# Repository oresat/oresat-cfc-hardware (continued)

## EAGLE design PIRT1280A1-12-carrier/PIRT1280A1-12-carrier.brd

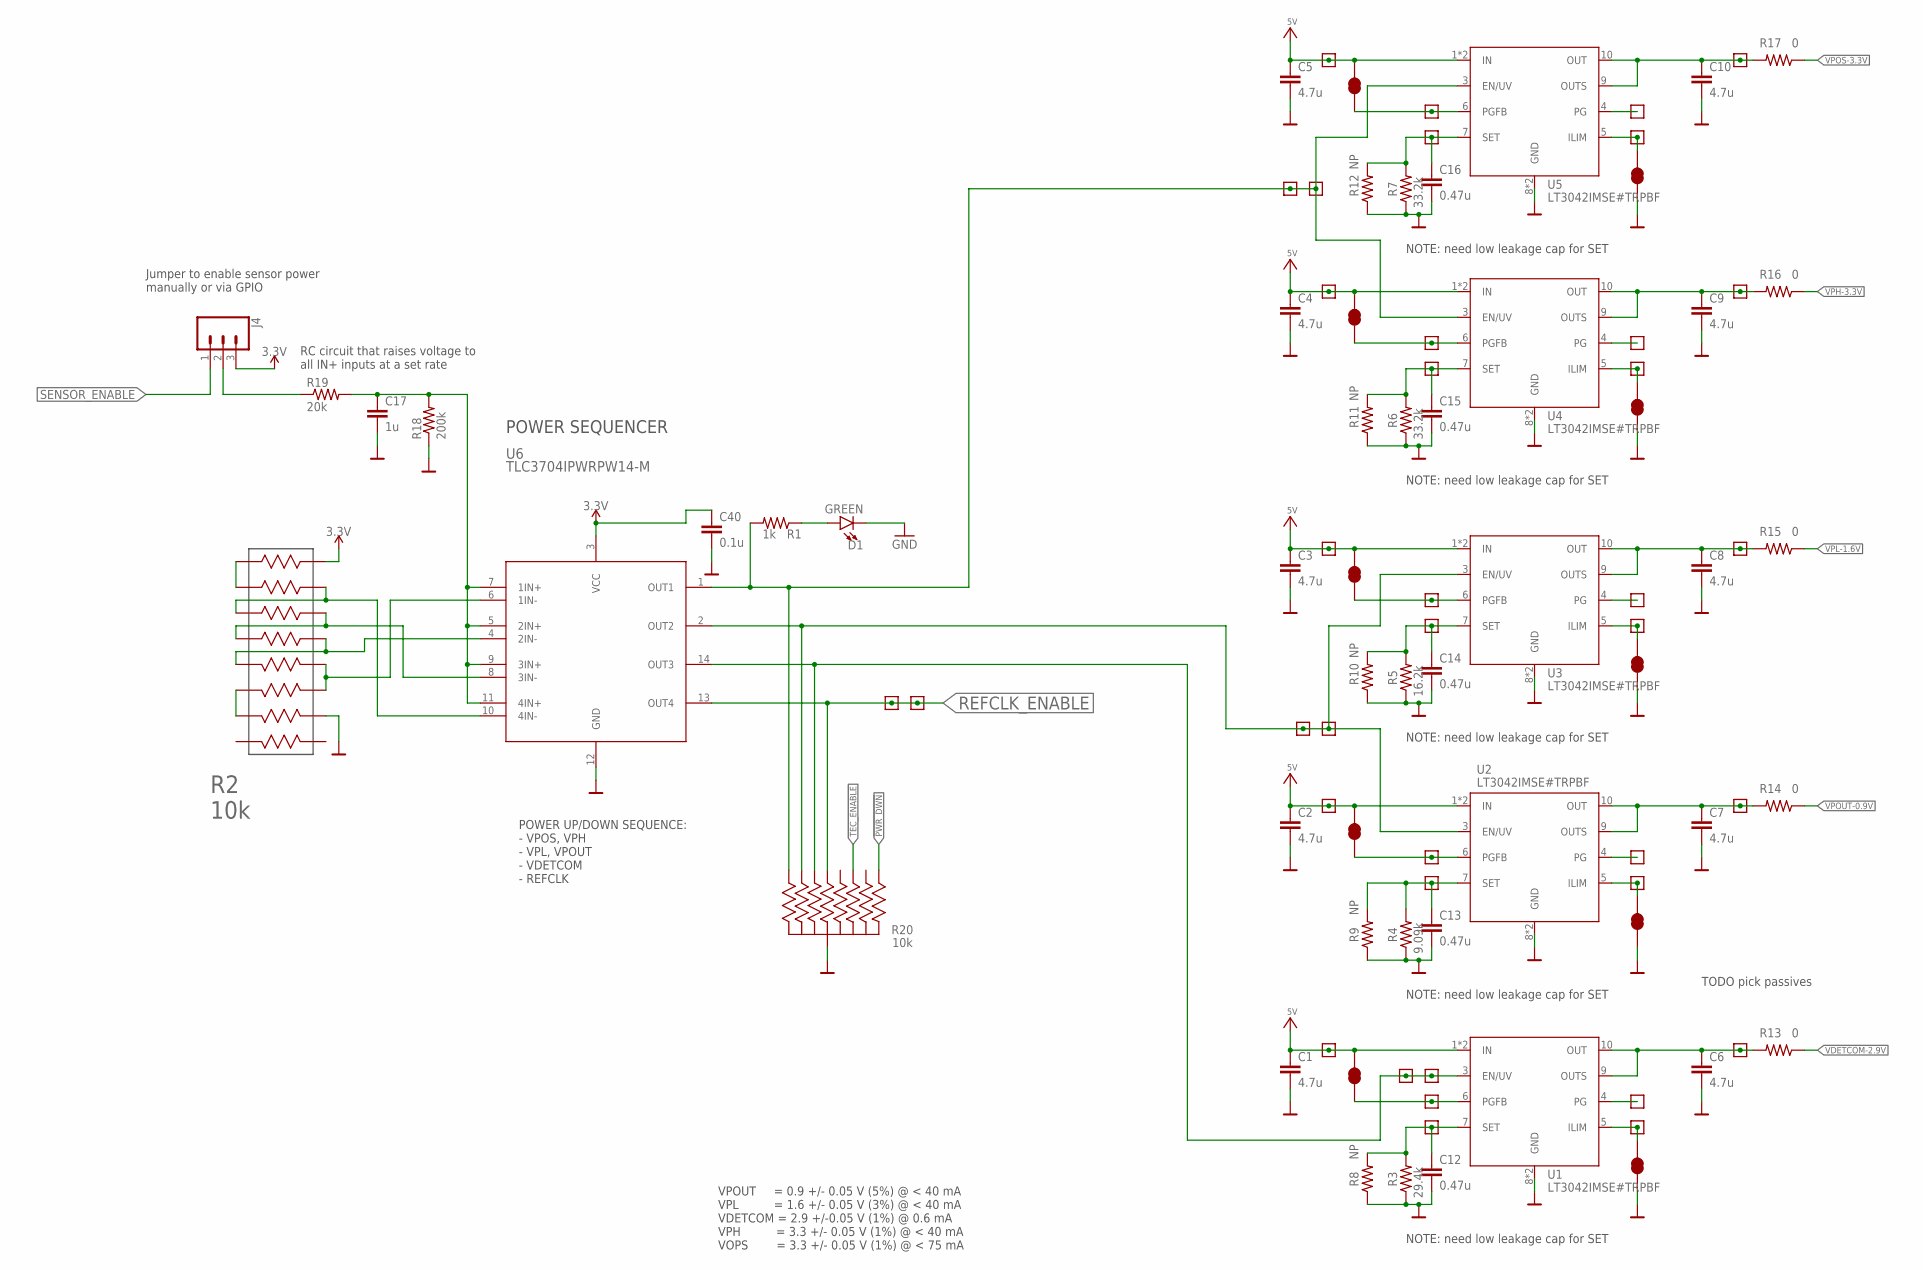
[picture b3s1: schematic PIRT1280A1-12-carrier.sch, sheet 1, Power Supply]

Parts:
C1, C2, C3, C4, C5, C6, C7, C8, C9, C10: 4.7u; .0603-A
C12, C13, C14, C15, C16: 0.47u; .0603-A
C17: 1u; .0603-A
C40: 0.1u; .0603-A
D1: GREEN; LED-0603; MANUFACTURER_PART_NUMBER 150060VS55040; DIGI-KEY_PART_NUMBER 732-12017-1-ND
J4: 455-1750-1-ND; 1X03
R1: 1k; .0603-A
R2: 10k; RES_EXB2HV
R3: 29.4k; .0603-A
R4: 9.09k; .0603-A
R5: 16.2k; .0603-A
R6, R7: 33.2k; .0603-A
R8, R9, R10, R11, R12: NP; .0603-A
R13, R14, R15, R16, R17: 0; .0603-A
R18: 200k; .0805-A
R19: 20k; .0805-A
R20: 10k; ARRAY_EXBA-M; MPN EXB-A10P103J
SJ1, SJ2, SJ3, SJ4, SJ5, SJ6, SJ7, SJ8, SJ9, SJ10: JUMPER-SMT_2_NC_TRACE_NO-SILK; SMT-JUMPER_2_NC_TRACE_NO-SILK
TP1, TP2, TP3, TP4, TP5, TP6, TP7, TP8, TP9, TP10, TP11, TP12, TP13, TP14, TP15, TP16, TP17, TP18, TP19, TP20, TP21, TP22, TP23, TP24, TP25, TP26, TP27, TP28, TP29, TP30, TP31, TP32, TP33, TP34, TP35, TP36, TP37, TP38: TEST-POINT-LARGE-SQUARE; 1X01
U1, U2, U3, U4, U5: LT3042IMSE#TRPBF; SOP50P490X110-11N
U6: TLC3704IPWRPW14-M; 14-TSSOP

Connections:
3.3V: C40.1, J4.3, R2.16, U6.3 (VCC); also elsewhere on the board
5V: C1.1, C2.1, C3.1, C4.1, C5.1, SJ6.2, SJ7.2, SJ8.2, SJ9.2, SJ10.2, TP3.1, TP6.1, TP9.1, TP12.1, TP15.1, U1.1 (IN), U1.2 (IN), U2.1 (IN), U2.2 (IN), U3.1 (IN), U3.2 (IN), U4.1 (IN), U4.2 (IN), U5.1 (IN), U5.2 (IN); also elsewhere on the board
!PWR_DWN: R20.1 (11); also elsewhere on the board
GND: C1.2, C2.2, C3.2, C4.2, C5.2, C6.2, C7.2, C8.2, C9.2, C10.2, C12.2, C13.2, C14.2, C15.2, C16.2, C17.2, C40.2, D1.C, R2.10, R3.1, R4.1, R5.1, R6.1, R7.1, R8.1, R9.1, R10.1, R11.1, R12.1, R18.1, R20.5 (55), R20.10 (55), SJ1.1, SJ2.1, SJ3.1, SJ4.1, SJ5.1, U1.8 (GND), U1.11 (GND), U2.8 (GND), U2.11 (GND), U3.8 (GND), U3.11 (GND), U4.8 (GND), U4.11 (GND), U5.8 (GND), U5.11 (GND), U6.12 (GND); also elsewhere on the board
unnamed: R2.1, R2.2
unnamed: R2.3, R2.15, U6.10 (4IN-)
unnamed: R2.4, R2.14, U6.8 (3IN-)
unnamed: R2.5, R2.13, U6.4 (2IN-)
unnamed: C17.1, R18.2, R19.2, U6.5 (2IN+), U6.7 (1IN+), U6.9 (3IN+), U6.11 (4IN+)
unnamed: R2.6, R2.7
unnamed: R20.7 (77), TP20.1, TP21.1, U1.3 (EN/UV), U6.14 (OUT3)
unnamed: SJ7.1, TP31.1, U2.6 (PGFB)
unnamed: SJ2.2, TP4.1, U2.5 (ILIM)
unnamed: TP5.1, U2.4 (PG)
unnamed: J4.2, R19.1
unnamed: C13.1, R4.2, R9.2, TP32.1, U2.7 (SET)
unnamed: SJ1.2, TP1.1, U1.5 (ILIM)
unnamed: SJ6.1, TP29.1, U1.6 (PGFB)
unnamed: TP2.1, U1.4 (PG)
unnamed: C12.1, R3.2, R8.2, TP30.1, U1.7 (SET)
unnamed: R1.2, R20.6 (66), TP16.1, TP17.1, U4.3 (EN/UV), U5.3 (EN/UV), U6.1 (OUT1)
unnamed: SJ5.2, TP13.1, U5.5 (ILIM)
unnamed: SJ10.1, TP37.1, U5.6 (PGFB)
unnamed: TP14.1, U5.4 (PG)
unnamed: C16.1, R7.2, R12.2, TP38.1, U5.7 (SET)
unnamed: SJ4.2, TP10.1, U4.5 (ILIM)
unnamed: SJ9.1, TP35.1, U4.6 (PGFB)
unnamed: TP11.1, U4.4 (PG)
unnamed: C15.1, R6.2, R11.2, TP36.1, U4.7 (SET)
unnamed: R20.4 (44), TP18.1, TP19.1, U2.3 (EN/UV), U3.3 (EN/UV), U6.2 (OUT2)
unnamed: SJ3.2, TP7.1, U3.5 (ILIM)
unnamed: SJ8.1, TP33.1, U3.6 (PGFB)
unnamed: TP8.1, U3.4 (PG)
unnamed: C14.1, R5.2, R10.2, TP34.1, U3.7 (SET)
unnamed: R2.11, R2.12, U6.6 (1IN-)
unnamed: D1.A, R1.1
REFCLK_ENABLE: R20.3 (33), TP27.1, TP28.1, U6.13 (OUT4); also elsewhere on the board
SENSOR_ENABLE: J4.1; also elsewhere on the board
TEC_ENABLE: R20.2 (22); also elsewhere on the board
VDETCOM: C6.1, R13.2, TP22.1, U1.9 (OUTS), U1.10 (OUT)
VDETCOM-2.9V: R13.1; also elsewhere on the board
VPH: C9.1, R16.2, TP25.1, U4.9 (OUTS), U4.10 (OUT)
VPH-3.3V: R16.1; also elsewhere on the board
VPL: C8.1, R15.2, TP24.1, U3.9 (OUTS), U3.10 (OUT)
VPL-1.6V: R15.1; also elsewhere on the board
VPOS: C10.1, R17.2, TP26.1, U5.9 (OUTS), U5.10 (OUT)
VPOS-3.3V: R17.1; also elsewhere on the board
VPOUT: C7.1, R14.2, TP23.1, U2.9 (OUTS), U2.10 (OUT)
VPOUT-0.9V: R14.1; also elsewhere on the board

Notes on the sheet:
VPOUT = 0.9 +/- 0.05 V (5%) @ < 40 mA VPL = 1.6 +/- 0.05 V (3%) @ < 40 mA VDETCOM = 2.9 +/-0.05 V (1%) @ 0.6 mA VPH = 3.3 +/- 0.05 V (1%) @ < 40 mA VOPS = 3.3 +/- 0.05 V (1%) @ < 75 mA
NOTE: need low leakage cap for SET
TODO pick passives
POWER UP/DOWN SEQUENCE: - VPOS, VPH - VPL, VPOUT - VDETCOM - REFCLK
RC circuit that raises voltage to all IN+ inputs at a set rate
Jumper to enable sensor power manually or via GPIO
POWER SEQUENCER

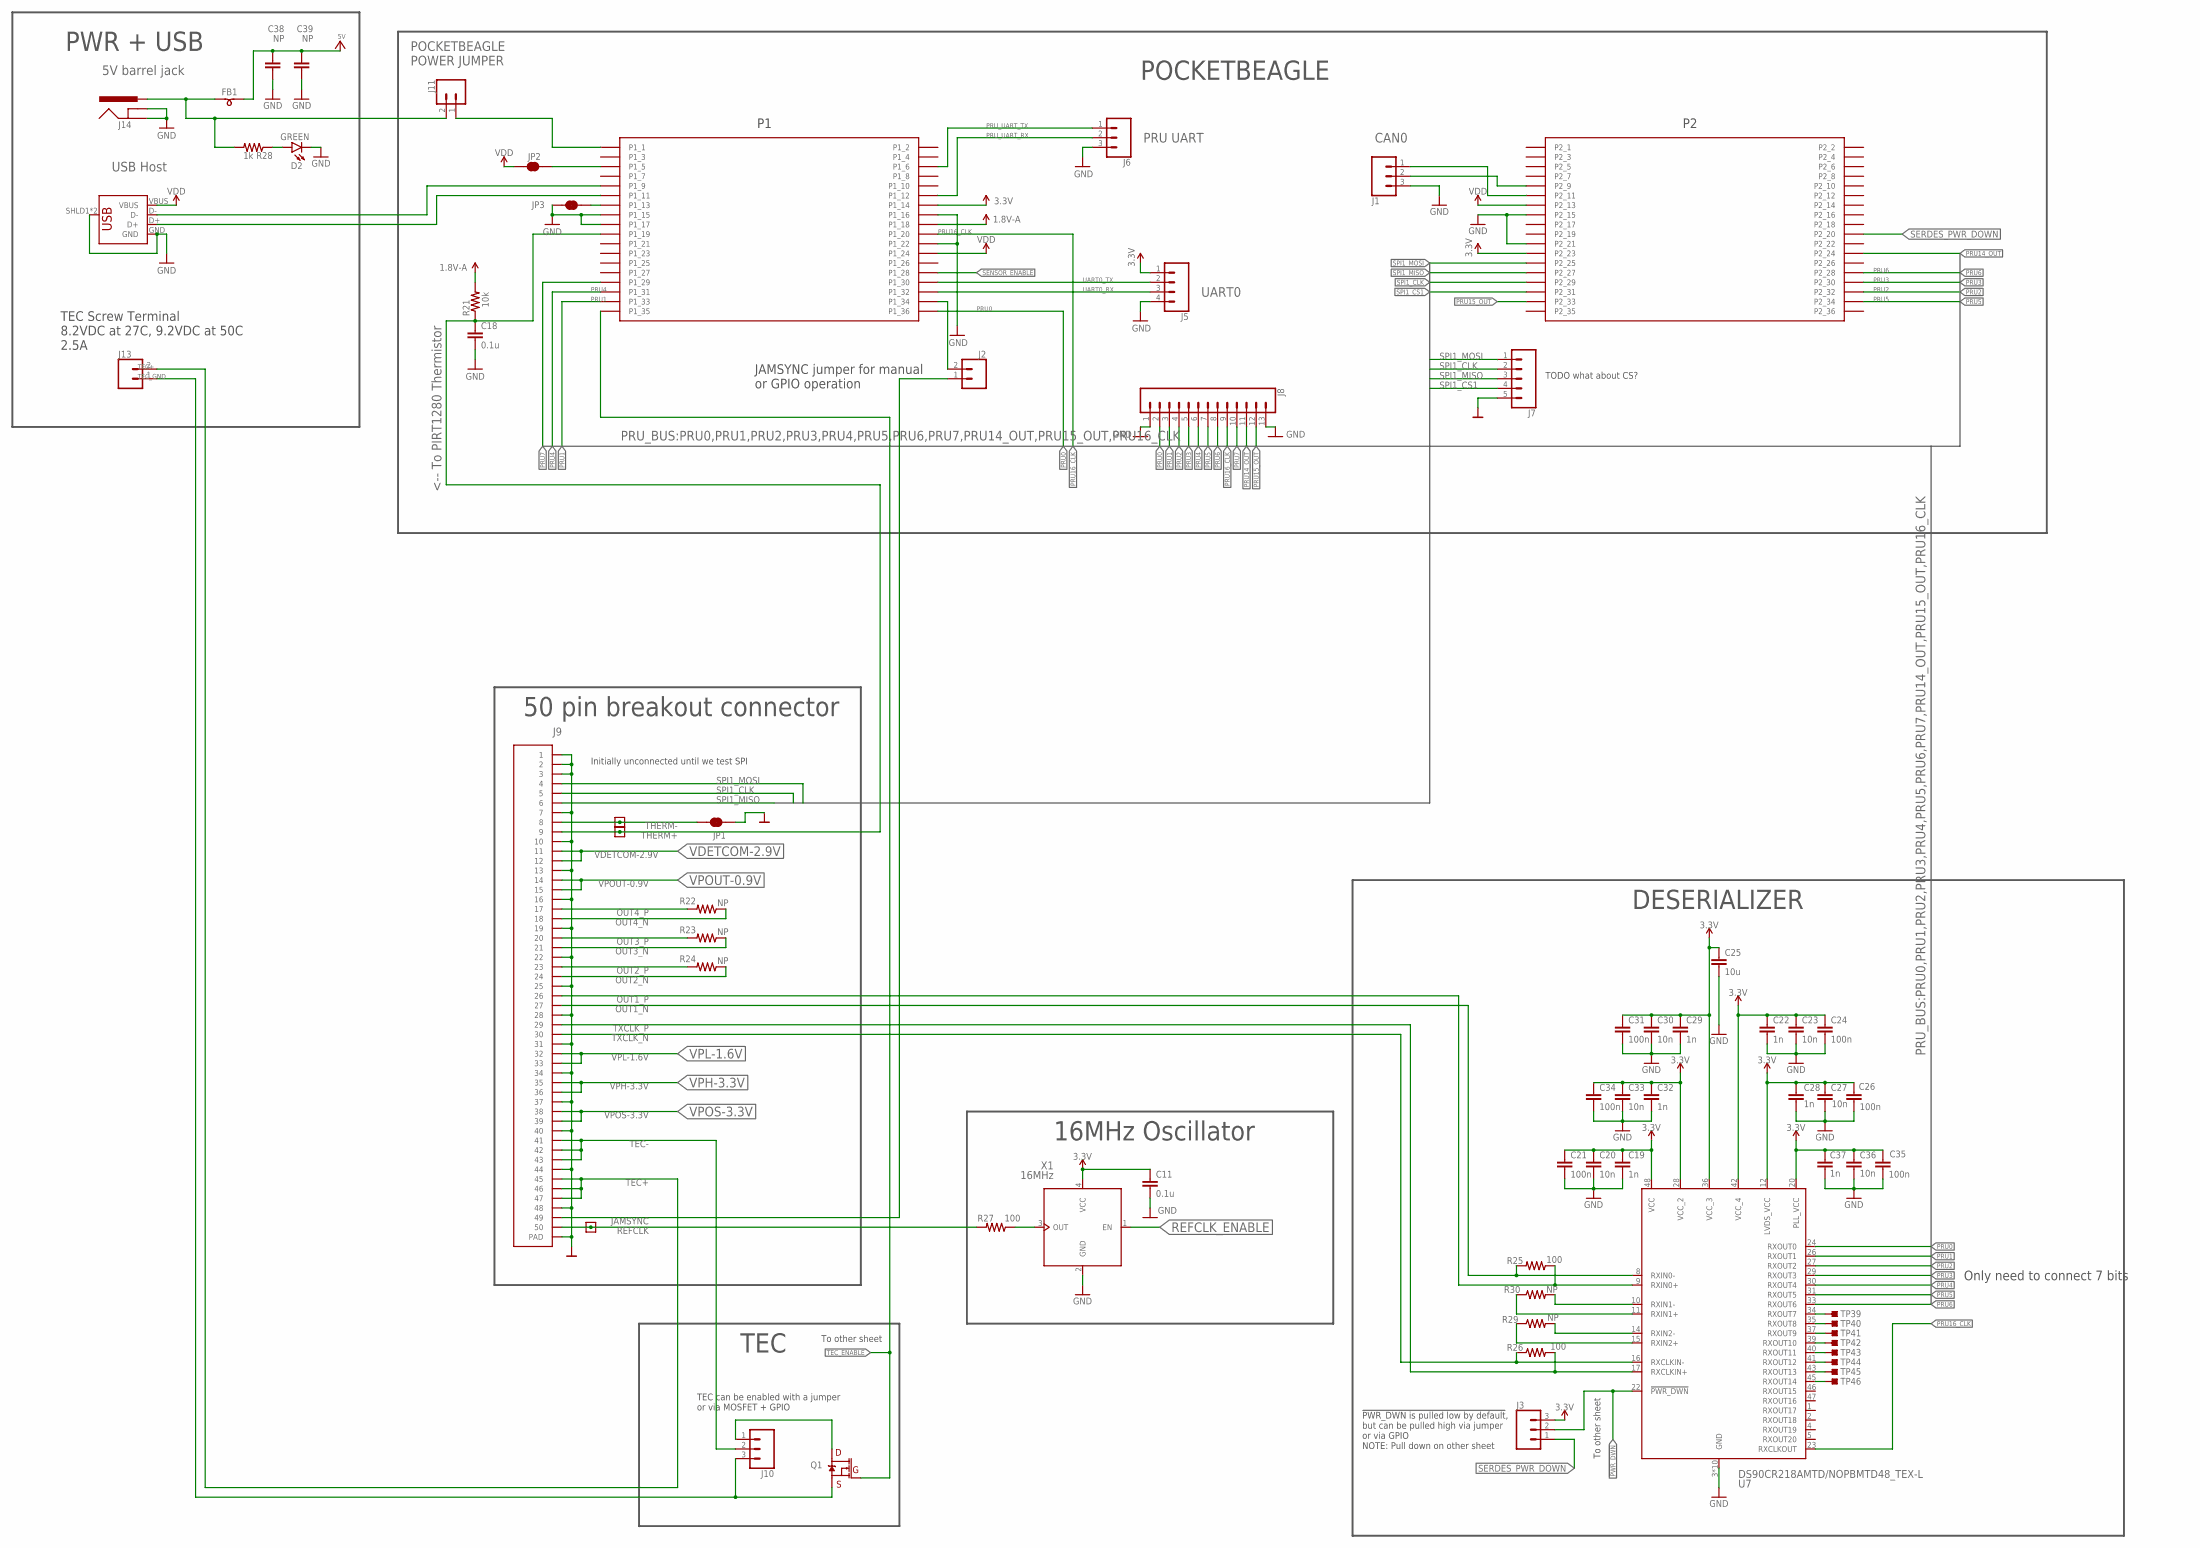
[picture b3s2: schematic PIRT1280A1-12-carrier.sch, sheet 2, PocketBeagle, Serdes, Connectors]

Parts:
C11, C18: 0.1u; .0603-A
C19, C22, C28, C29, C32, C37: 1n; .0402-C-NOSILK; MPN GRM155R71H102KA01J
C20, C23, C27, C30, C33, C36: 10n; .0402-C-NOSILK; MPN C0603C103M5RACTU
C21, C24, C26, C31, C34, C35: 100n; .0402-C-NOSILK; MPN C0805C104Z5VACTU
C25: 10u; .0603-C-NOSILK; MPN GRM188R61A106KE69J
C38, C39: NP; C1210
D2: GREEN; LED-0603; MANUFACTURER_PART_NUMBER 150060VS55040; DIGI-KEY_PART_NUMBER 732-12017-1-ND
FB1: L-BEAD-0805-B; .0805-B
J1, J3, J6, J10: 455-1750-1-ND; 1X03
J2, J11: CONN_02; 1X02
J5: CONN_04PTH; 1X04
J7: CONN_05; 1X05
J8: CONN_13; 1X13
J9: 5-1734592-0; TE_5-1734592-0
J12: USB_A_SMT_FEMALE; USB-A-S-SILK-FEMALE; MANUFACTURER_PART_NUMBER PRT-09011; MOUSER_PART_NUMBER 474-PRT-09011
J13: 5MM_SCREW_TERMINAL5MM; SCREWTERMINAL-5MM-2; MPN 0395430002
J14: POWER_JACK
JP1, JP2, JP3: JUMPER-SMT_2_NC_TRACE_NO-SILK; SMT-JUMPER_2_NC_TRACE_NO-SILK
Q1: 35A/25V/8.5mΩ; DPAK
R21: 10k; .0603-A
R22, R23, R24, R29, R30: NP; .0402-C-NOSILK; MPN RC0201FR-07100RL
R25, R26, R27: 100; .0402-C-NOSILK; MPN RC0201FR-07100RL
R28: 1k; .0603-A
REFCLK: TEST-POINT-LARGE-SQUARE; 1X01
THERM+: TEST-POINT-LARGE-SQUARE; 1X01
THERM-: TEST-POINT-LARGE-SQUARE; 1X01
TP39, TP40, TP41, TP42, TP43, TP44, TP45, TP46: TEST-POINT-SMD-0.5MM; TESTPOINT_SMD-0.5MM
U7: DS90CR218AMTD/NOPBMTD48_TEX-L; MTD48_TEX-L
U$2: POCKETBEAGLE
X1: 16MHz; OSC_2.5X2.0

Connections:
1.8V-A: R21.2, U$2.P1_18
3.3V: C11.1, C19.1, C20.1, C21.1, C22.1, C23.1, C24.1, C25.1, C26.1, C27.1, C28.1, C29.1, C30.1, C31.1, C32.1, C33.1, C34.1, C35.1, C36.1, C37.1, J3.3, J5.1, U7.12 (LVDS_VCC), U7.20 (PLL_VCC), U7.28 (VCC_2), U7.36 (VCC_3), U7.42 (VCC_4), U7.48 (VCC), U$2.P1_14, U$2.P2_23, X1.4 (VCC); also elsewhere on the board
5V: C38.1, C39.1, FB1.2; also elsewhere on the board
!PWR_DWN: J3.2, U7.22 (!PWR_DWN); also elsewhere on the board
CAN_RX: J1.2, U$2.P2_9
CAN_TX: J1.1, U$2.P2_11
GND: C11.2, C18.2, C19.2, C20.2, C21.2, C22.2, C23.2, C24.2, C25.2, C26.2, C27.2, C28.2, C29.2, C30.2, C31.2, C32.2, C33.2, C34.2, C35.2, C36.2, C37.2, C38.2, C39.2, D2.C, J1.3, J5.4, J6.3, J7.5, J8.1, J8.13, J9.1, J9.2, J9.3, J9.7, J9.10, J9.13, J9.16, J9.19, J9.22, J9.25, J9.28, J9.31, J9.34, J9.37, J9.40, J9.44, J9.48, J9.S1 (PAD), J9.S2 (PAD), J12.GND, J12.SHLD1 (SHIELD), J12.SHLD2 (SHIELD), J14.GND, J14.GNDBREAK, JP1.1, JP3.2, U7.3 (GND), U7.7 (GND), U7.13 (GND), U7.18 (GND), U7.19 (GND), U7.21 (GND), U7.25 (GND), U7.32 (GND), U7.38 (GND), U7.44 (GND), U$2.P1_15, U$2.P1_16, U$2.P1_17, U$2.P1_22, U$2.P2_15, U$2.P2_21, X1.2 (GND); also elsewhere on the board
JAMSYNC: J2.1, J9.49
unnamed: FB1.1, J11.2, J14.PWR, R28.2
unnamed: JP2.1, U$2.P1_5
unnamed: R27.1, X1.3 (OUT)
unnamed: R29.2, U7.14 (RXIN2-)
unnamed: R29.1, U7.15 (RXIN2+)
unnamed: JP3.1, U$2.P1_13
unnamed: R30.2, U7.10 (RXIN1-)
unnamed: R30.1, U7.11 (RXIN1+)
unnamed: J11.1, U$2.P1_1
unnamed: D2.A, R28.1
unnamed: TP39.TP, U7.34 (RXOUT7)
unnamed: TP40.TP, U7.35 (RXOUT8)
unnamed: TP41.TP, U7.37 (RXOUT9)
unnamed: TP42.TP, U7.39 (RXOUT10)
unnamed: TP43.TP, U7.40 (RXOUT11)
unnamed: TP44.TP, U7.41 (RXOUT12)
unnamed: TP45.TP, U7.43 (RXOUT13)
unnamed: TP46.TP, U7.45 (RXOUT14)
unnamed: J2.2, U$2.P1_34
unnamed: J10.1, Q1.4 (D)
OUT1_N: J9.27, R25.2, U7.8 (RXIN0-)
OUT1_P: J9.26, R25.1, U7.9 (RXIN0+)
OUT2_N: J9.24, R24.1
OUT2_P: J9.23, R24.2
OUT3_N: J9.21, R23.1
OUT3_P: J9.20, R23.2
OUT4_N: J9.18, R22.1
OUT4_P: J9.17, R22.2
PRU0: J8.2, U7.24 (RXOUT0), U$2.P1_36
PRU1: J8.3, U7.26 (RXOUT1), U$2.P1_33
PRU2: J8.4, U7.27 (RXOUT2), U$2.P2_32
PRU3: J8.5, U7.29 (RXOUT3), U$2.P2_30
PRU4: J8.6, U7.30 (RXOUT4), U$2.P1_31
PRU5: J8.7, U7.31 (RXOUT5), U$2.P2_34
PRU6: J8.8, U7.33 (RXOUT6), U$2.P2_28
PRU7: J8.10, U$2.P1_29
PRU14_OUT: J8.11, U$2.P2_24
PRU15_OUT: J8.12, U$2.P2_33
PRU16_CLK: J8.9, U7.23 (RXCLKOUT), U$2.P1_20
PRU_UART_RX: J6.2, U$2.P1_12
PRU_UART_TX: J6.1, U$2.P1_6
REFCLK: J9.50, R27.2, REFCLK.1
REFCLK_ENABLE: X1.1 (EN); also elsewhere on the board
SENSOR_ENABLE: U$2.P1_28; also elsewhere on the board
SERDES_PWR_DOWN: J3.1, U$2.P2_20
SPI1_CLK: J7.2, J9.5, U$2.P2_29
SPI1_CS1: J7.4, U$2.P2_31
SPI1_MISO: J7.3, J9.6, U$2.P2_27
SPI1_MOSI: J7.1, J9.4, U$2.P2_25
TEC+: J9.45, J9.46, J9.47, J13.2
TEC-: J9.41, J9.42, J9.43, J10.2
TEC_ENABLE: Q1.1 (G), U$2.P1_35; also elsewhere on the board
TEC_GND: J10.3, J13.1, Q1.3 (S)
THERM+: C18.1, J9.9, R21.1, THERM+.1, U$2.P1_19
THERM-: J9.8, JP1.2, THERM-.1
TXCLK_N: J9.30, R26.1, U7.16 (RXCLKIN-)
TXCLK_P: J9.29, R26.2, U7.17 (RXCLKIN+)
UART0_RX: J5.3, U$2.P1_32
UART0_TX: J5.2, U$2.P1_30
USB_N: J12.D-, U$2.P1_9
USB_P: J12.D+, U$2.P1_11
VDD: J12.VBUS, JP2.2, U$2.P1_24, U$2.P2_13
VDETCOM-2.9V: J9.11, J9.12; also elsewhere on the board
VPH-3.3V: J9.35, J9.36; also elsewhere on the board
VPL-1.6V: J9.32, J9.33; also elsewhere on the board
VPOS-3.3V: J9.38, J9.39; also elsewhere on the board
VPOUT-0.9V: J9.14, J9.15; also elsewhere on the board

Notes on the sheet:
TODO what about CS?
5V barrel jack
USB Host
UART0
<-- To PIRT1280 Thermistor
Only need to connect 7 bits
PRU UART
CAN0
Initially unconnected until we test SPI
TEC
TEC can be enabled with a jumper or via MOSFET + GPIO
JAMSYNC jumper for manual or GPIO operation
TEC Screw Terminal 8.2VDC at 27C, 9.2VDC at 50C 2.5A
!PWR_DWN is pulled low by default, but can be pulled high via jumper or via GPIO NOTE: Pull down on other sheet
To other sheet
16MHz Oscillator
50 pin breakout connector
DESERIALIZER
PWR + USB
POCKETBEAGLE
POCKETBEAGLE POWER JUMPER

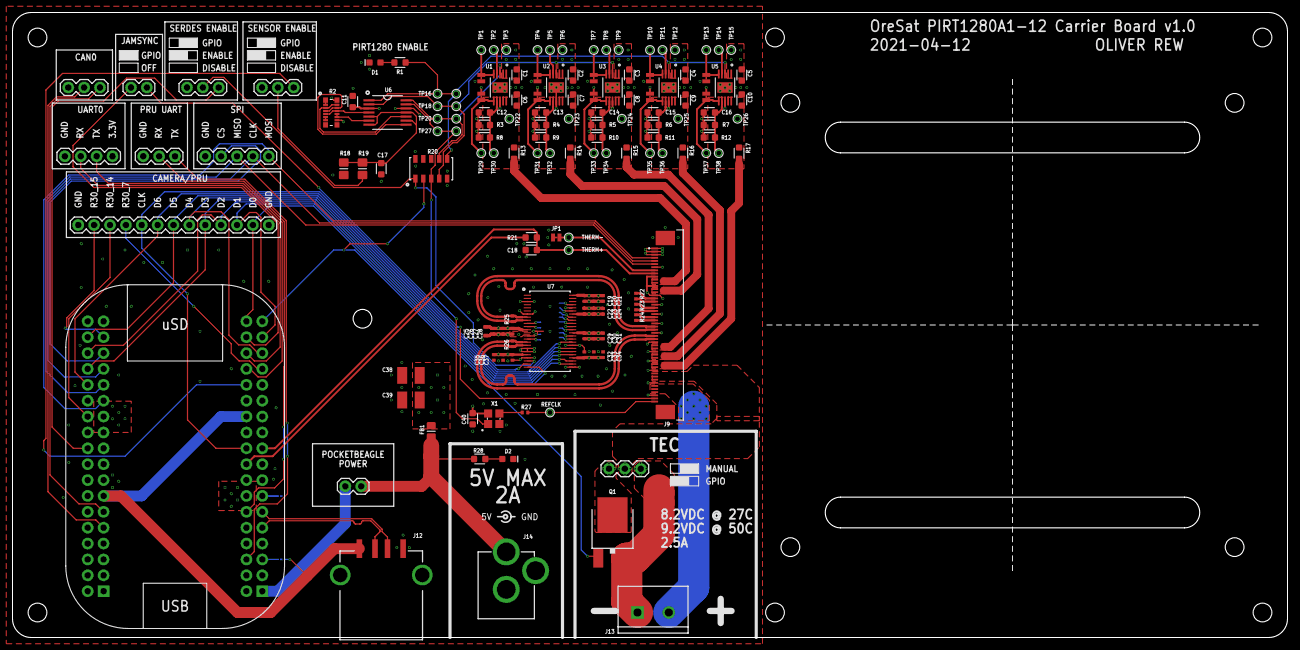
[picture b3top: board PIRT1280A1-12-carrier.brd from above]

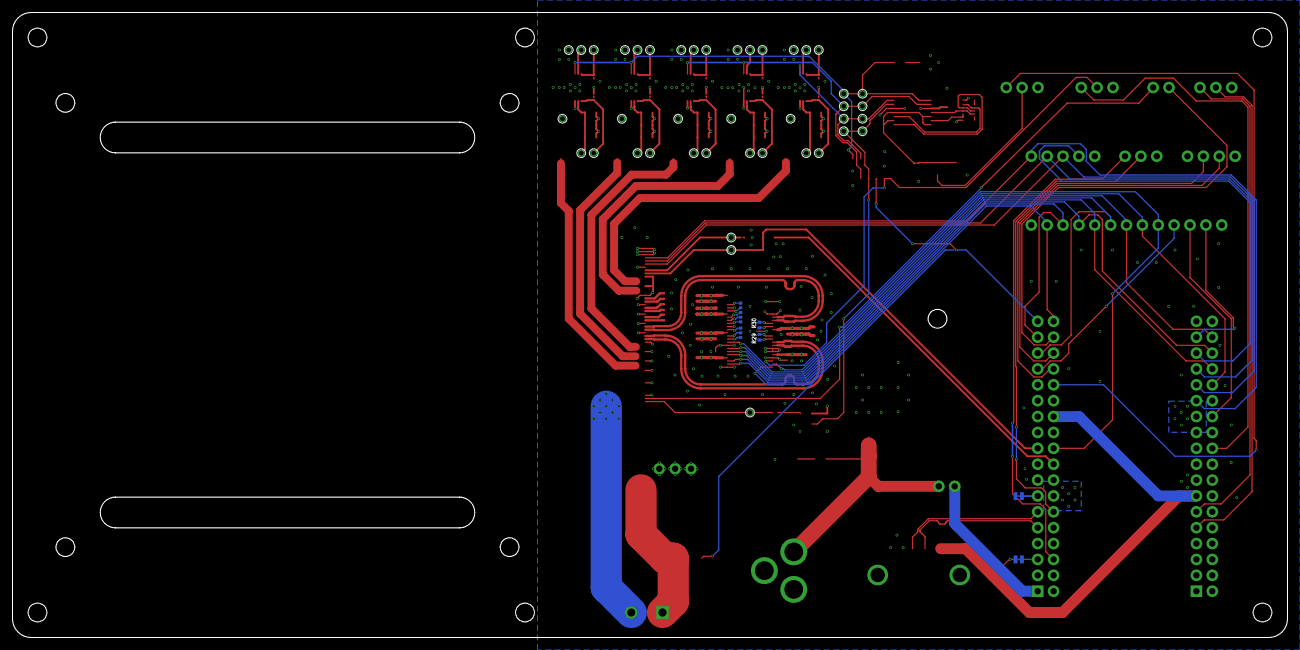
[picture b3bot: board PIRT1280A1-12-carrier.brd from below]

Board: 4 copper layers, 204.0 x 100.0 mm, 161 parts (12 on the bottom side), 112 nets.

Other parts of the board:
U$1: PIRT1280_BREAKOUT
U$3: POLARITY_SYMBOL_SMALL

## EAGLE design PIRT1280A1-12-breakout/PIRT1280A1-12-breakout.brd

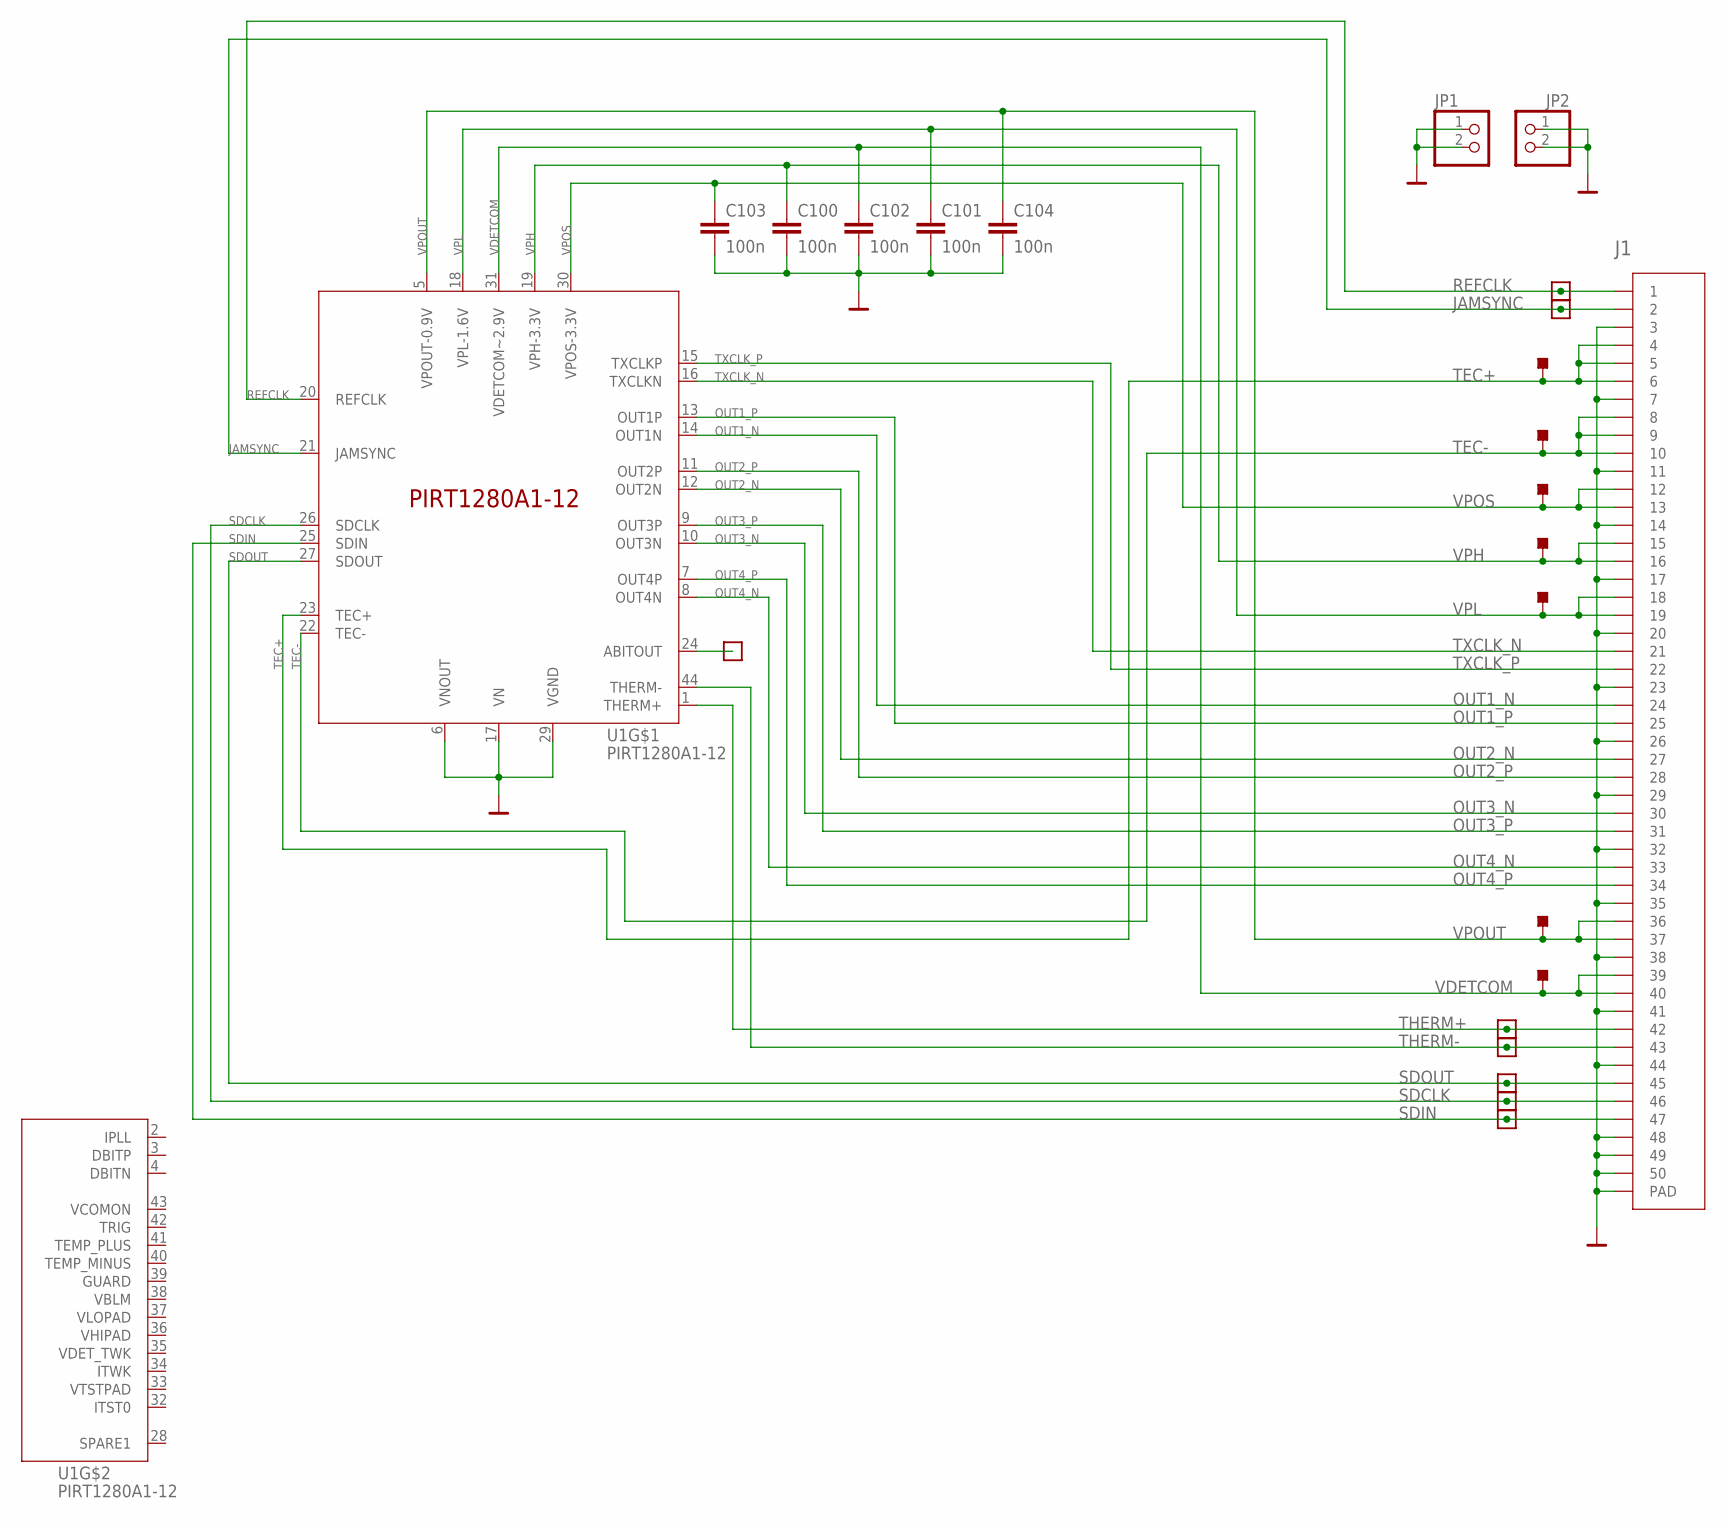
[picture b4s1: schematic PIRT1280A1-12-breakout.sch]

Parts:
C100, C101, C102, C103, C104: 100n; .0805-A
J1: 5-1734592-0; TE_5-1734592-0
JAMSYNC: TEST-POINT-LARGE-SQUARE; 1X01
JP1, JP2: PINHD-1X2; 1X02
REFCLK: TEST-POINT-LARGE-SQUARE; 1X01
SDCLK: TEST-POINT-LARGE-SQUARE; 1X01
SDIN: TEST-POINT-LARGE-SQUARE; 1X01
SDOUT: TEST-POINT-LARGE-SQUARE; 1X01
TEC+: TEST-POINT_SMD-SMD-10SN; TESTPOINT_SMD-10SN
TEC-: TEST-POINT_SMD-SMD-10SN; TESTPOINT_SMD-10SN
THERM+: TEST-POINT-LARGE-SQUARE; 1X01
THERM-: TEST-POINT-LARGE-SQUARE; 1X01
TP1: TEST-POINT-LARGE-SQUARE; 1X01
U1: PIRT1280A1-12
VDETCOM: TEST-POINT_SMD-SMD-10SN; TESTPOINT_SMD-10SN
VPH: TEST-POINT_SMD-SMD-10SN; TESTPOINT_SMD-10SN
VPL: TEST-POINT_SMD-SMD-10SN; TESTPOINT_SMD-10SN
VPOS: TEST-POINT_SMD-SMD-10SN; TESTPOINT_SMD-10SN
VPOUT: TEST-POINT_SMD-SMD-10SN; TESTPOINT_SMD-10SN

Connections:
ABITOUT: TP1.1, U1.24 (ABITOUT)
GND: C100.2, C101.2, C102.2, C103.2, C104.2, J1.3, J1.7, J1.11, J1.14, J1.17, J1.20, J1.23, J1.26, J1.29, J1.32, J1.35, J1.38, J1.41, J1.44, J1.48, J1.49, J1.50, J1.S1 (PAD), J1.S2 (PAD), JP1.1, JP1.2, JP2.1, JP2.2, U1.6 (VNOUT), U1.17 (VN), U1.29 (VGND)
JAMSYNC: J1.2, JAMSYNC.1, U1.21 (JAMSYNC)
OUT1_N: J1.24, U1.14 (OUT1N)
OUT1_P: J1.25, U1.13 (OUT1P)
OUT2_N: J1.27, U1.12 (OUT2N)
OUT2_P: J1.28, U1.11 (OUT2P)
OUT3_N: J1.30, U1.10 (OUT3N)
OUT3_P: J1.31, U1.9 (OUT3P)
OUT4_N: J1.33, U1.8 (OUT4N)
OUT4_P: J1.34, U1.7 (OUT4P)
REFCLK: J1.1, REFCLK.1, U1.20 (REFCLK)
SDCLK: J1.46, SDCLK.1, U1.26 (SDCLK)
SDIN: J1.47, SDIN.1, U1.25 (SDIN)
SDOUT: J1.45, SDOUT.1, U1.27 (SDOUT)
TEC+: J1.4, J1.5, J1.6, TEC+.TP, U1.23 (TEC+)
TEC-: J1.8, J1.9, J1.10, TEC-.TP, U1.22 (TEC-)
THERM+: J1.42, THERM+.1, U1.1 (THERM+)
THERM-: J1.43, THERM-.1, U1.44 (THERM-)
TXCLK_N: J1.21, U1.16 (TXCLKN)
TXCLK_P: J1.22, U1.15 (TXCLKP)
VDETCOM: C102.1, J1.39, J1.40, U1.31 (VDETCOM~2.9V), VDETCOM.TP
VPH: C100.1, J1.15, J1.16, U1.19 (VPH-3.3V), VPH.TP
VPL: C101.1, J1.18, J1.19, U1.18 (VPL-1.6V), VPL.TP
VPOS: C103.1, J1.12, J1.13, U1.30 (VPOS-3.3V), VPOS.TP
VPOUT: C104.1, J1.36, J1.37, U1.5 (VPOUT-0.9V), VPOUT.TP

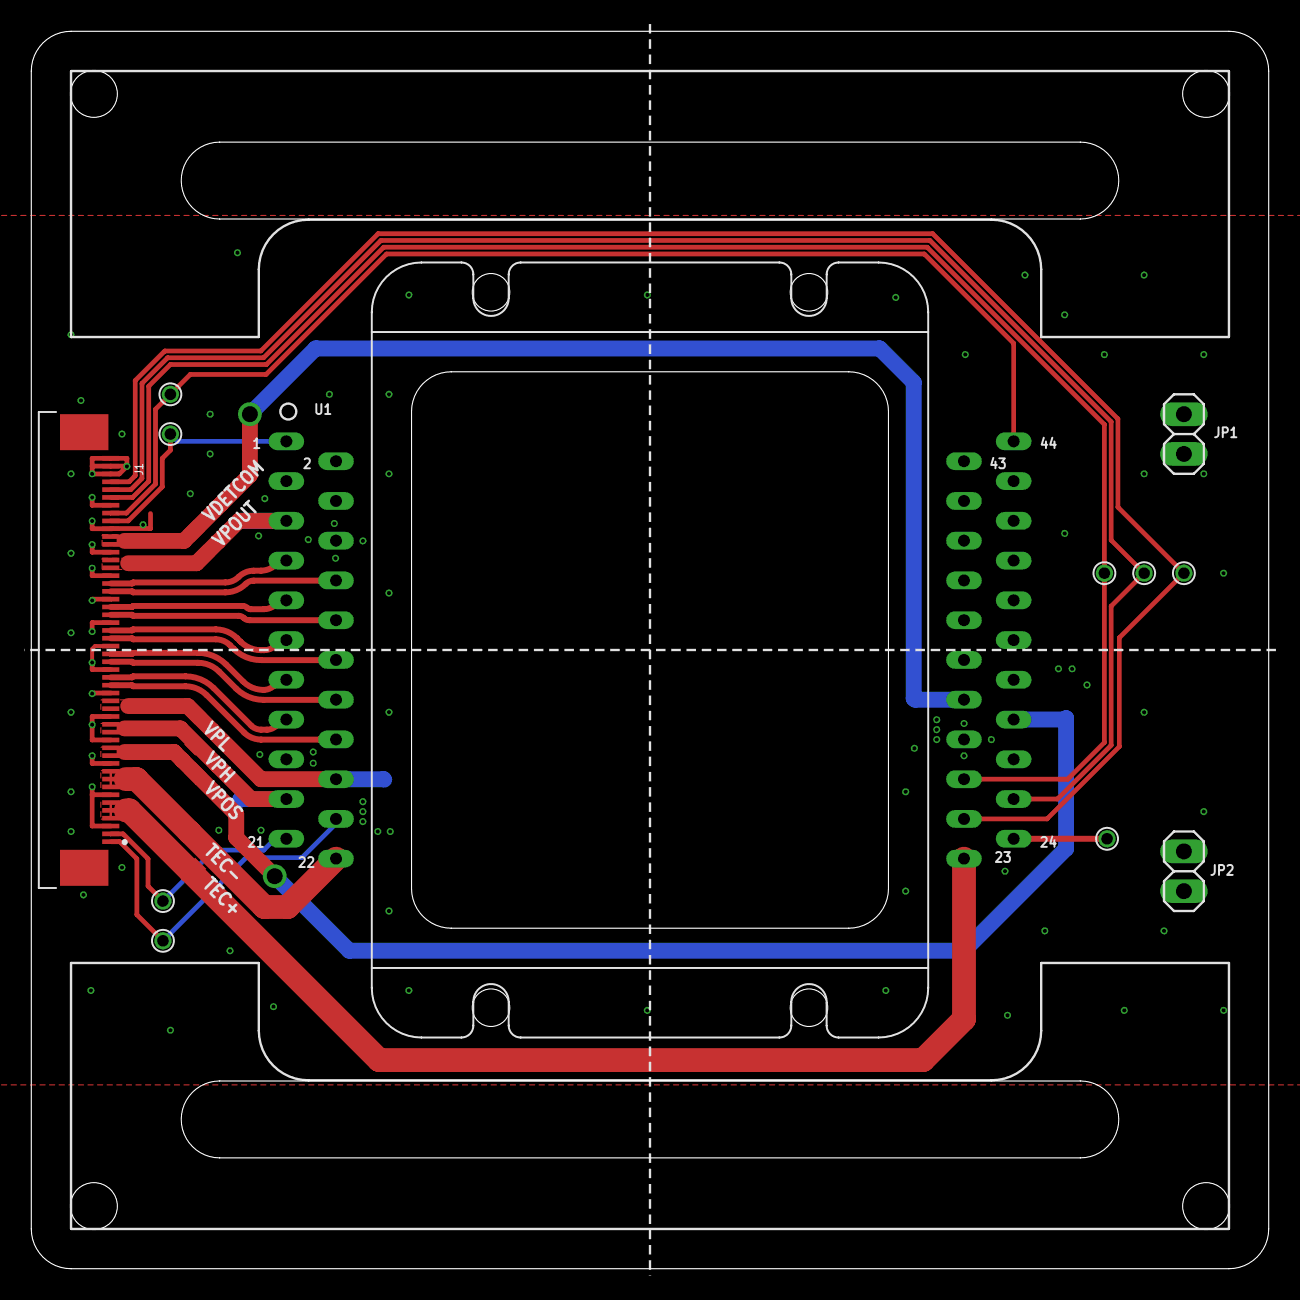
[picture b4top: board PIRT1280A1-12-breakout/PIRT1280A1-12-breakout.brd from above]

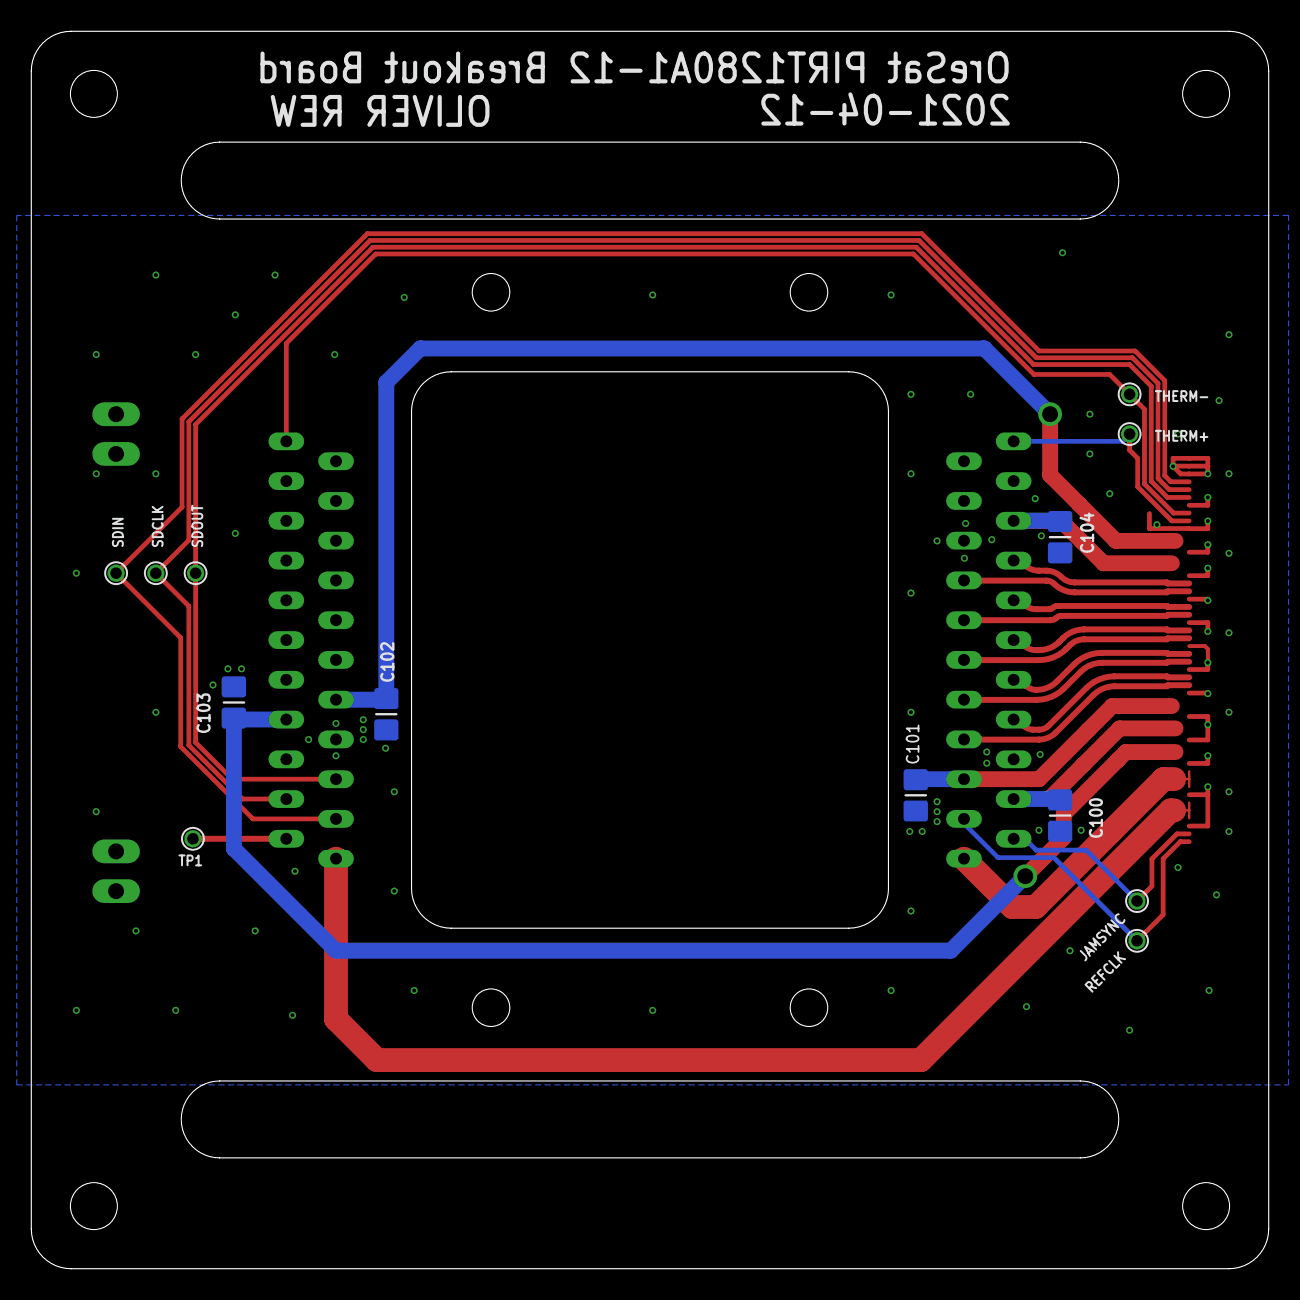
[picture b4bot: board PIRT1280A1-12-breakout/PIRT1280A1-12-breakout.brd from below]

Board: 4 copper layers, 79.1 x 79.1 mm, 24 parts (5 on the bottom side), 26 nets.

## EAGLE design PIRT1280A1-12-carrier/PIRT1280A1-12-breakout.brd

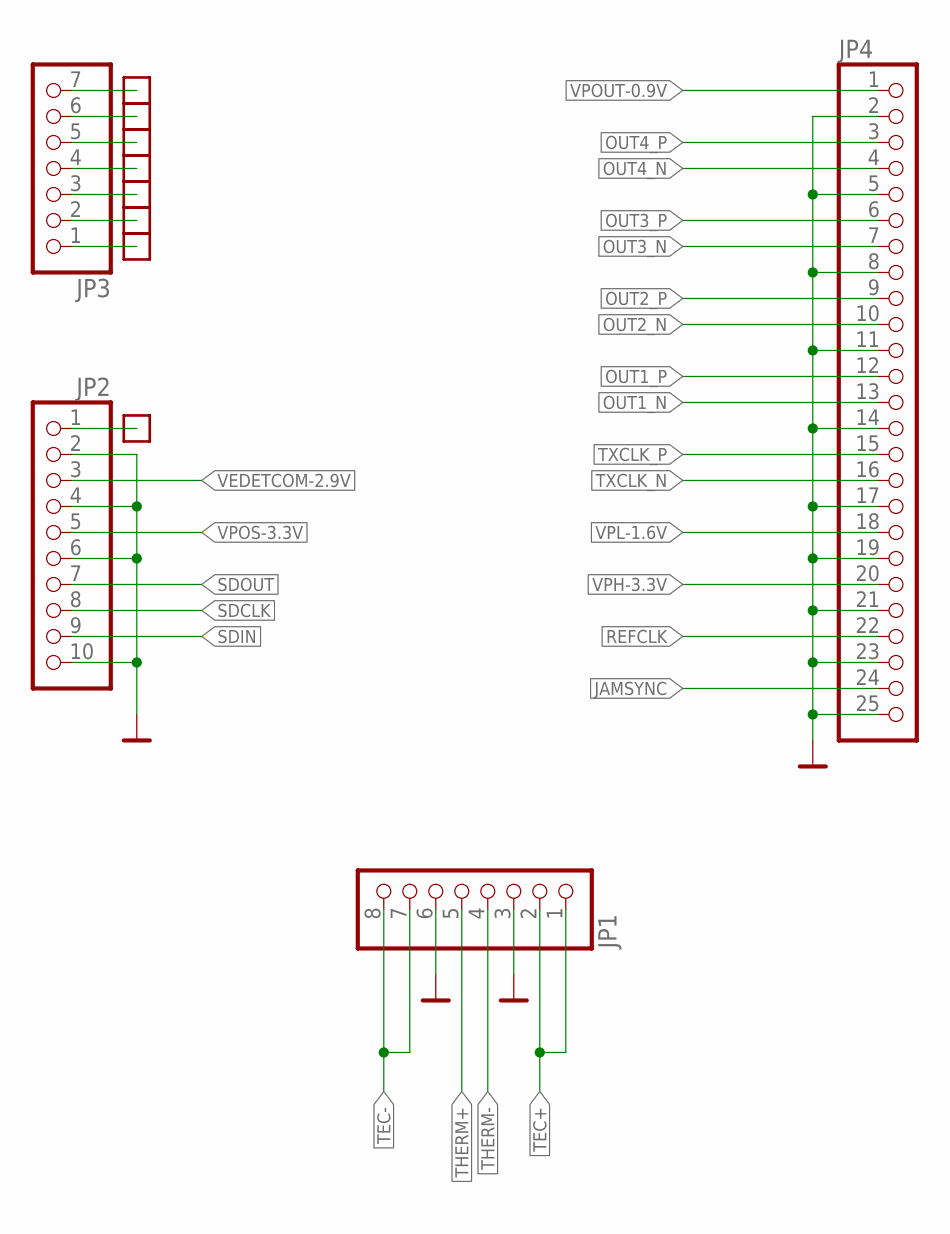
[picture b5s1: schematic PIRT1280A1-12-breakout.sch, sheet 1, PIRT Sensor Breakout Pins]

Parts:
JP1: PINHD-1X8; 1X08
JP2: PINHD-1X10; 1X10
JP3: PINHD-1X7; 1X07
JP4: PINHD-1X25; 1X25
TP2, TP3, TP4, TP5, TP6, TP7, TP8, TP9: TEST-POINT-LARGE-SQUARE; 1X01

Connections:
GND: JP1.3, JP1.6, JP2.2, JP2.4, JP2.6, JP2.10, JP4.2, JP4.5, JP4.8, JP4.11, JP4.14, JP4.17, JP4.19, JP4.21, JP4.23, JP4.25; also elsewhere on the board
JAMSYNC: JP4.24
unnamed: JP2.1, TP2.1
unnamed: JP3.7, TP9.1
unnamed: JP3.6, TP8.1
unnamed: JP3.5, TP7.1
unnamed: JP3.4, TP6.1
unnamed: JP3.3, TP5.1
unnamed: JP3.2, TP4.1
unnamed: JP3.1, TP3.1
OUT1_N: JP4.13
OUT1_P: JP4.12
OUT2_N: JP4.10
OUT2_P: JP4.9
OUT3_N: JP4.7
OUT3_P: JP4.6
OUT4_N: JP4.4
OUT4_P: JP4.3
REFCLK: JP4.22
SDCLK: JP2.8
SDIN: JP2.9
SDOUT: JP2.7
TEC+: JP1.1, JP1.2
TEC-: JP1.7, JP1.8
THERM+: JP1.5
THERM-: JP1.4
TXCLK_N: JP4.16
TXCLK_P: JP4.15
VEDETCOM-2.9V: JP2.3
VPH-3.3V: JP4.20
VPL-1.6V: JP4.18
VPOS-3.3V: JP2.5
VPOUT-0.9V: JP4.1; also elsewhere on the board
